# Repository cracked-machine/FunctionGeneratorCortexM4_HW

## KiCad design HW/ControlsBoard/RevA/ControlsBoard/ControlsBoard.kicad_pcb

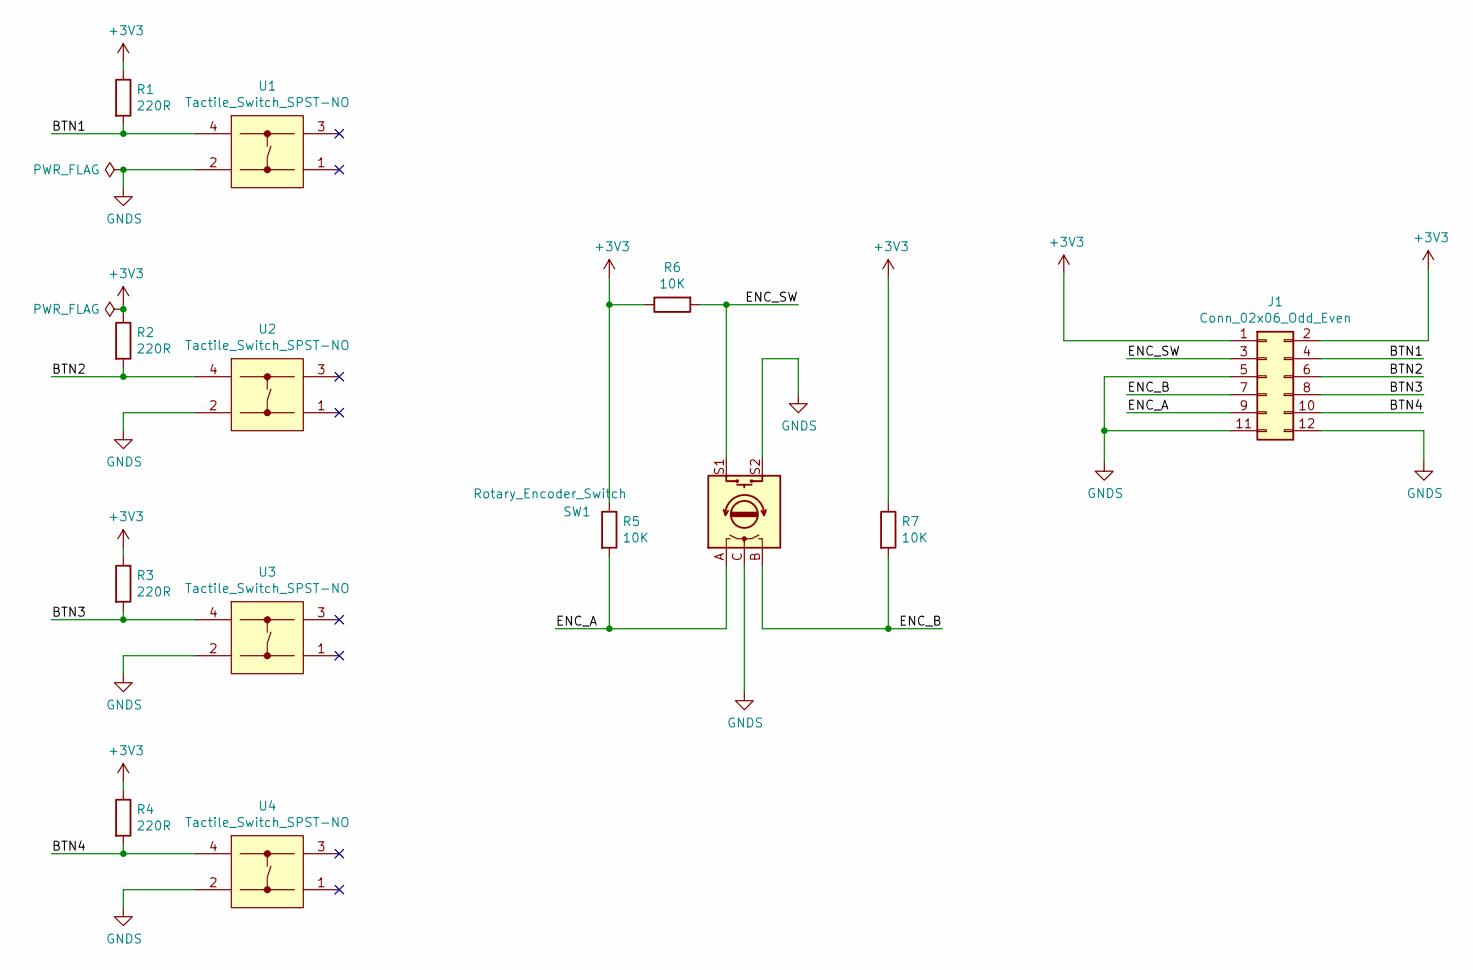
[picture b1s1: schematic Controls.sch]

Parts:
J1: Conn_02x06_Odd_Even; PinSocket_2x06_P2.54mm_Vertical_SMD
R1, R2, R3, R4: 220R; R_0805_2012Metric_Pad1.15x1.40mm_HandSolder
R5, R6, R7: 10K; R_1206_3216Metric_Pad1.42x1.75mm_HandSolder
SW1: Rotary_Encoder_Switch; RotaryEncoder_Alps_EC11E-Switch_Vertical_H20mm
U1, U2, U3, U4: Tactile_Switch_SPST-NO; 12x12x7_3mmTactilePushButtonMomentary

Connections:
+3V3: J1.1, J1.2, R1.1, R2.1, R3.1, R4.1, R5.1, R6.1, R7.1
/Controls/BTN1: J1.4, R1.2, U1.4
/Controls/BTN2: J1.6, R2.2, U2.4
/Controls/BTN3: J1.8, R3.2, U3.4
/Controls/BTN4: J1.10, R4.2, U4.4
/Controls/ENC_A: J1.9, R5.2, SW1.A
/Controls/ENC_B: J1.7, R7.2, SW1.B
/Controls/ENC_SW: J1.3, R6.2, SW1.S1
GNDS: J1.5, J1.11, J1.12, SW1.C, SW1.S2, U1.2, U2.2, U3.2, U4.2

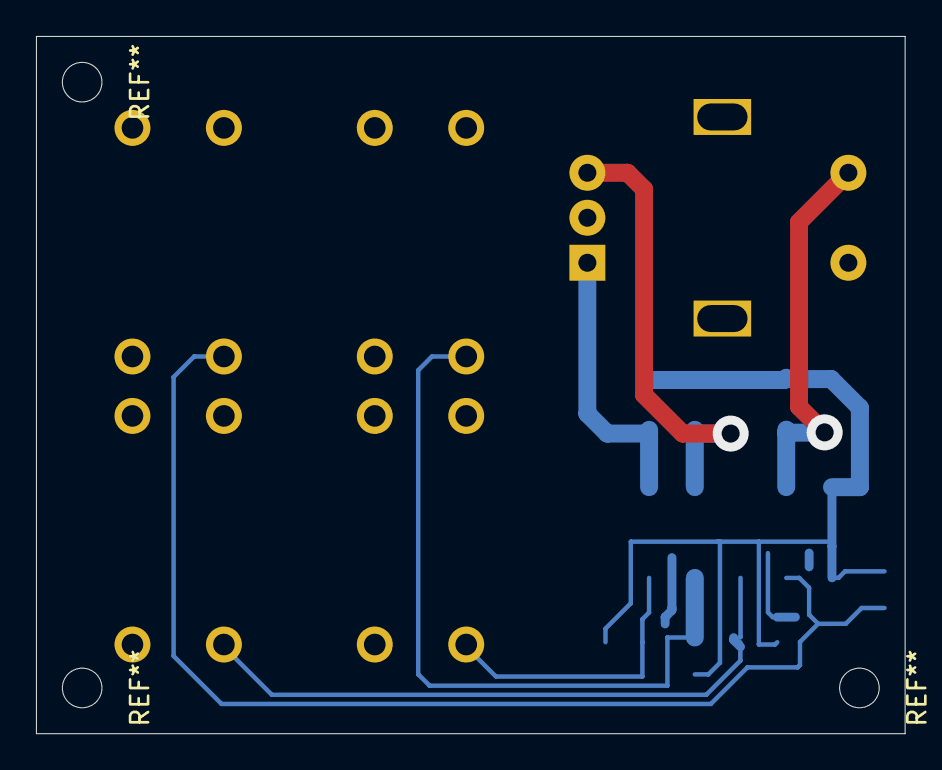
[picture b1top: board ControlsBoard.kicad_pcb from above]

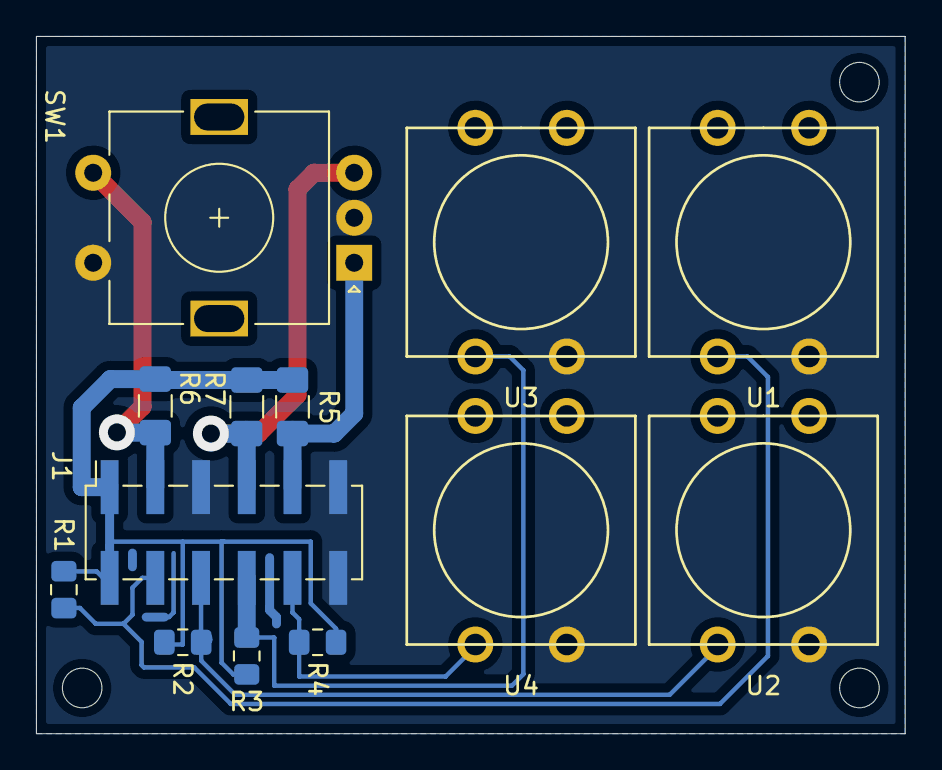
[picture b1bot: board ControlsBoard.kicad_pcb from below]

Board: 2 copper layers, 48.3 x 38.7 mm, 13 parts (13 on the bottom side), 9 nets.

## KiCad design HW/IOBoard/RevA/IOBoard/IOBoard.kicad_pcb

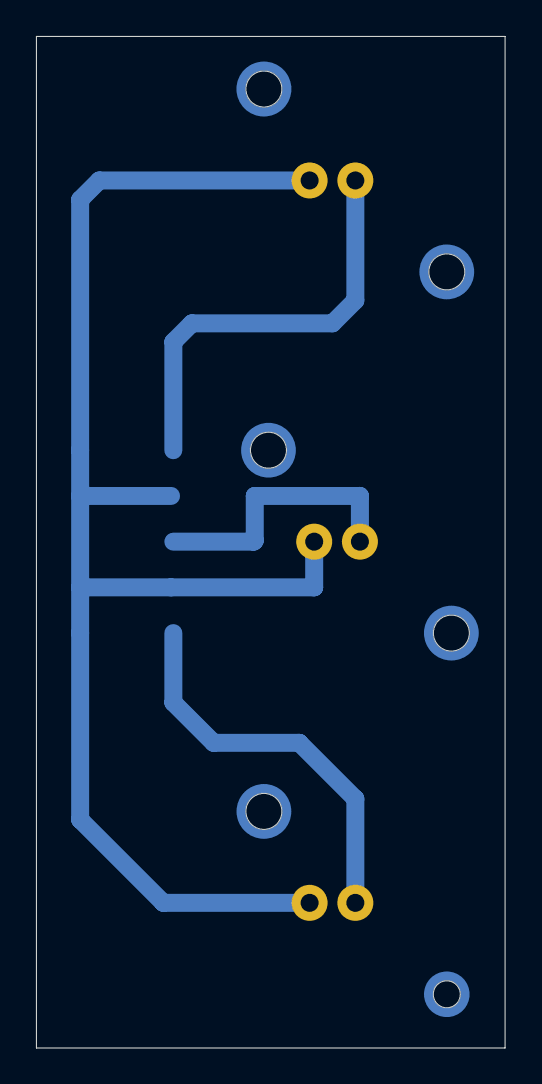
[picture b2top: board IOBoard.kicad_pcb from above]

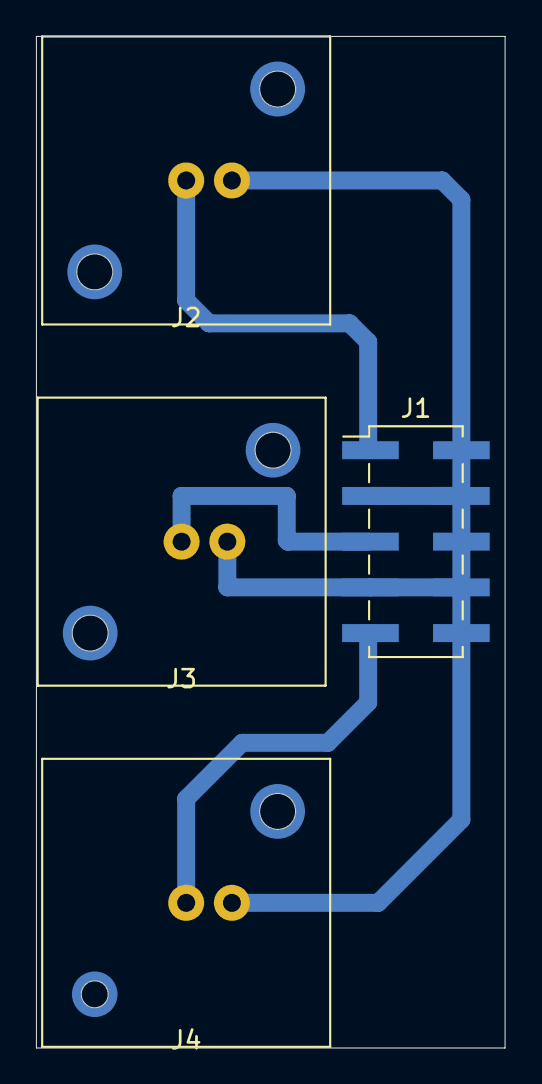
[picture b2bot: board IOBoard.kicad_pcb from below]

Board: 2 copper layers, 26.0 x 56.2 mm, 4 parts (4 on the bottom side), 4 nets.

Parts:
J1: Conn_02x05_Odd_Even; PinHeader_2x05_P2.54mm_Vertical_SMD
J2, J3, J4: Conn_Coaxial; RSProStraight50OhmPCBMountBulkheadFittingBNC_5260279

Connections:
/FUNC_SIG_OUT: J1.5, J3.1
/FUNC_SYNC_OUT: J1.1, J2.1
/TRIG_SIG_IN: J1.9, J4.1
GNDS: J1.2, J1.3, J1.4, J1.6, J1.7, J1.8, J1.10, J2.2, J3.2, J4.2
